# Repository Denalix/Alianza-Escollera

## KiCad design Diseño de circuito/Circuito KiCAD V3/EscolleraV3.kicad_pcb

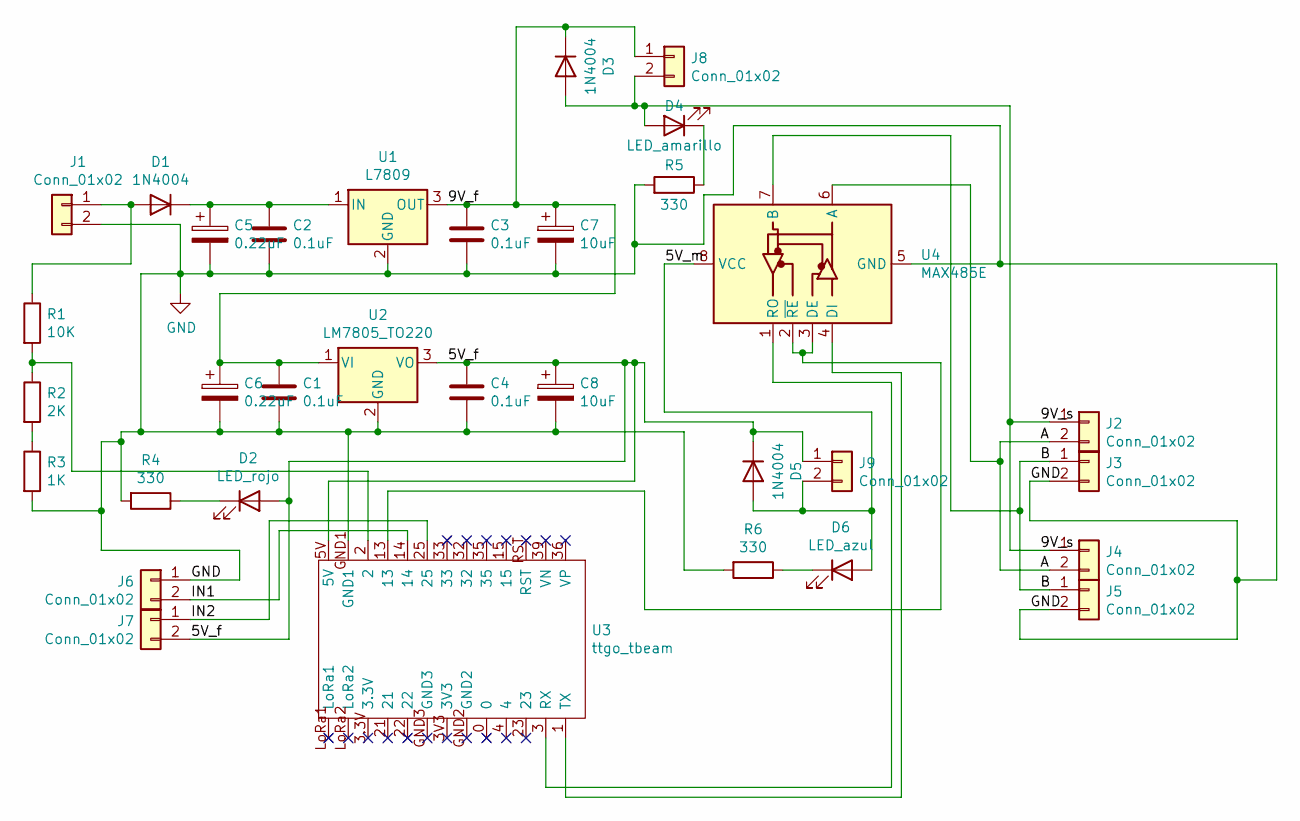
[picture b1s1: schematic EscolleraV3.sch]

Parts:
C1, C2, C3, C4: 0.1uF; C_Disc_D4.7mm_W2.5mm_P5.00mm
C5, C6: 0.22uF; C_Radial_D5.0mm_H11.0mm_P2.00mm
C7, C8: 10uF; C_Radial_D5.0mm_H11.0mm_P2.00mm
D1, D3, D5: 1N4004; D_DO-41_SOD81_P3.81mm_Vertical_AnodeUp
D2: LED_rojo; LED_D3.0mm
D4: LED_amarillo; LED_D3.0mm
D6: LED_azul; LED_D3.0mm
J1, J2, J3, J4, J5, J6, J7, J8, J9: Conn_01x02; bornera
R1: 10K; R_Axial_DIN0207_L6.3mm_D2.5mm_P7.62mm_Horizontal
R2: 2K; R_Axial_DIN0207_L6.3mm_D2.5mm_P7.62mm_Horizontal
R3: 1K; R_Axial_DIN0207_L6.3mm_D2.5mm_P7.62mm_Horizontal
R4, R5, R6: 330; R_Axial_DIN0207_L6.3mm_D2.5mm_P7.62mm_Horizontal
U1: L7809; TO-220-3_Vertical
U2: LM7805_TO220; TO-220-3_Vertical
U3: ttgo_tbeam
U4: MAX485E; max485_TTL_RS485

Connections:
/5V_f: C4.1, C8.1, D2.2 (A), D5.1 (K), J7.2, J9.1, U2.3 (VO), U3.5V
/5V_m: D5.2 (A), D6.2 (A), J9.2, U4.8 (VCC)
/9V_f: C1.1, C3.1, C6.1, C7.1, D3.1 (K), J8.1, U1.3 (OUT), U2.1 (VI)
/9V_s: D3.2 (A), D4.2 (A), J2.1, J4.1, J8.2
/A: J2.2, J4.2, U4.6 (A)
/B: J3.1, J5.1, U4.7 (B)
/IN1: J6.2, U3.14
/IN2: J7.1, U3.25
GND: C1.2, C2.2, C3.2, C4.2, C5.2, C6.2, C7.2, C8.2, J1.2, J3.2, J5.2, J6.1, R3.2, R4.2, R5.2, R6.2, U1.2 (GND), U2.2 (GND), U3.GND1, U4.5 (GND)
unnamed: C2.1, C5.1, D1.1 (K), U1.1 (IN)
unnamed: D1.2 (A), J1.1, R1.1
unnamed: D2.1 (K), R4.1
unnamed: D4.1 (K), R5.1
unnamed: D6.1 (K), R6.1
unnamed: R1.2, R2.1, U3.2
unnamed: R2.2, R3.1
unnamed: U3.1 (TX), U4.4 (DI)
unnamed: U3.3 (RX), U4.1 (RO)
unnamed: U3.13, U4.2 (~RE), U4.3 (DE)

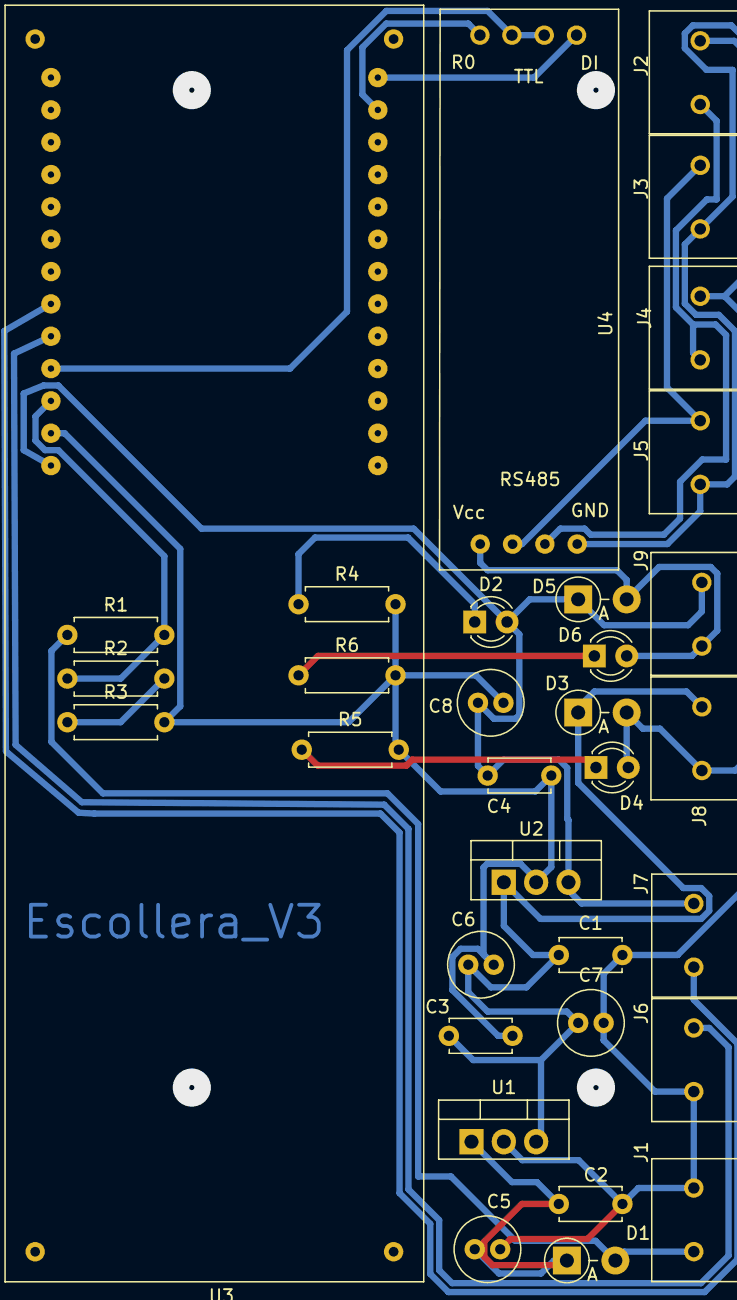
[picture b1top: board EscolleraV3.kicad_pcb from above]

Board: 2 copper layers, 33 parts (0 on the bottom side), 19 nets.

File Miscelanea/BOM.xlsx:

componente | imagen | Cantidad por boya | Precio estimado por unidad (pesos colombianos) | Total cantidad de elementos | Total precio por 3 boyas | Cantida de boyas | 3 | U2 | LM7805_TO220
MAX485 |  | 1 | 4500 | 3 | 13500 |  |  | J1 | Conn_01x02
LM7805 |  | 1 | 900 | 3 | 2700 |  |  | C2 | 0.1uF
LM7809 |  | 1 | 1000 | 3 | 3000 |  |  | C3 | 0.1uF
Condensador electrolítico 0.22 uF |  | 2 | 100 | 6 | 600 |  |  | C1 | 0.1uF
Condensador electrolítico 10 uF |  | 2 | 100 | 6 | 600 |  |  | C1 | 0.1uF
Condensador cerámico 104 (100nf o 0.1uf ) |  | 4 | 100 | 12 | 1200 |  |  | C4 | 0.1uF
Bornera de dos pines |  | 9 | 1000 | 27 | 27000 |  |  | U4 | MAX485E
Diodo 1N4004 |  | 3 | 100 | 9 | 900 |  |  | U3 | ttgo_tbeam
LED de chorro amarillo |  | 3 | 100 | 9 | 900 |  |  | U3 | ttgo_tbeam
LED de chorro rojo |  | 3 | 100 | 9 | 900 |  |  | U3 | ttgo_tbeam
LED de chorro azul |  | 3 | 100 | 9 | 900 |  |  | U3 | ttgo_tbeam
Resistencia 330 ohmios 1/4 de watt |  | 3 | 100 | 9 | 900 |  |  | U3 | ttgo_tbeam
Resistencia 1 kilo ohmio 1/4 de watt |  | 1 | 100 | 3 | 300 |  |  | U3 | ttgo_tbeam
Resistencia 10 kilo ohmios 1/4 de watt |  | 1 | 100 | 3 | 300 |  |  | U3 | ttgo_tbeam
Resistencia 2 kilo ohmios 1/4 de watt |  | 1 | 100 | 3 | 300 |  |  | U3 | ttgo_tbeam
módulo relé de dos canáles |  | 1 | 12500 | 3 | 37500 |  |  | U3 | ttgo_tbeam
jumpers amarillos |  | 3 | 300 | 9 | 2700 |  |  | U3 | ttgo_tbeam
jumpers azules |  | 3 | 300 | 9 | 2700 |  |  | U3 | ttgo_tbeam
jumpers verdes |  | 3 | 300 | 9 | 2700 |  |  | U3 | ttgo_tbeam
jumpers naranja |  | 3 | 300 | 9 | 2700 |  |  | U3 | ttgo_tbeam
Regleta de Pines Header Macho - Hembra 1x40 2.54mm |  | 1 | 1000 | 3 | 3000 |  |  | U3 | ttgo_tbeam
Termoencogible 5 mm diámetro por metro |  | 1 | 1200 | 3 | 3600 |  |  | U3 | ttgo_tbeam
Termoencogible 5 mm diámetro por metro |  | 1 | 3000 | 3 | 9000 |  |  | U3 | ttgo_tbeam
Malla desoldadora |  | 1 | 6500 | 3 | 19500 |  |  | U3 | ttgo_tbeam
Carreta de Soldadura de Estaño Solder 30 gr |  | 1 | 11000 | 3 | 33000 |  |  | U3 | ttgo_tbeam
Cautín 40W HQ |  | 1 | 35000 | 3 | 105000 |  |  | U3 | ttgo_tbeam
Tercera Mano con Soporte para Cautín, Pinzas y Lupa |  | 1 | 35000 | 3 | 105000 |  |  | U3 | ttgo_tbeam
Pomada para Soldar "La Única" 8 gr |  | 1 | 3000 | 3 | 9000 |  |  | U3 | ttgo_tbeam
Extractor Removedor de Soldadura Estaño - Plomo ZD190 |  | 1 | 8000 | 3 | 24000 |  |  | U3 | ttgo_tbeam
Batería seca 12V 5Ah |  | 1 |  | 3 | 0 |  |  | U3 | ttgo_tbeam
Multimetro Digital Uni-t Referencia Ut33c+ |  | 1 | 63000 | 3 | 189000 |  |  | U3 | ttgo_tbeam
Pinza de Punta Larga 4 Pulgadas - Marca Ranger |  | 1 | 15000 | 3 | 45000 |  |  | U3 | ttgo_tbeam
Pinza de Punta Curva 4 Pulgadas - Marca Ranger |  | 1 | 12500 | 3 | 37500 |  |  | U3 | ttgo_tbeam
Cortafrio 4 Pulgadas - Marca Ranger |  | 1 | 12500 | 3 | 37500 |  |  | U3 | ttgo_tbeam
Pelacable Ajustable 5" Calibres 10 AWG ~ 30 AWG |  | 1 | 12500 | 3 | 37500 |  |  | U3 | ttgo_tbeam
Total |  |  |  | 198 | 759900 |  |  | C5 | 0.22uF
 |  |  |  |  |  |  |  | C7 | 10uF
 |  |  |  |  |  |  |  | C6 | 0.22uF
 |  |  |  |  |  |  |  | C8 | 10uF
 |  |  |  |  |  |  |  | J2 | Conn_01x02
 |  |  |  |  |  |  |  | J3 | Conn_01x02
 |  |  |  |  |  |  |  | J4 | Conn_01x02
 |  |  |  |  |  |  |  | J5 | Conn_01x02
 |  |  |  |  |  |  |  | U1 | L7809
 |  |  |  |  |  |  |  | D5 | 1N4004
 |  |  |  |  |  |  |  | D3 | 1N4004
 |  |  |  |  |  |  |  | D1 | 1N4004
 |  |  |  |  |  |  |  | J8 | Conn_01x02
 |  |  |  |  |  |  |  | J9 | Conn_01x02
 |  |  |  |  |  |  |  | J6 | Conn_01x02
 |  |  |  |  |  |  |  | J7 | Conn_01x02
 |  |  |  |  |  |  |  | D4 | LED
 |  |  |  |  |  |  |  | D2 | LED
 |  |  |  |  |  |  |  | D6 | LED
 |  |  |  |  |  |  |  | R6 | 330
 |  |  |  |  |  |  |  | R4 | 330
 |  |  |  |  |  |  |  | R1 | 10K
 |  |  |  |  |  |  |  | R2 | 2K
 |  |  |  |  |  |  |  | R3 | 1K
 |  |  |  |  |  |  |  | R5 | 330

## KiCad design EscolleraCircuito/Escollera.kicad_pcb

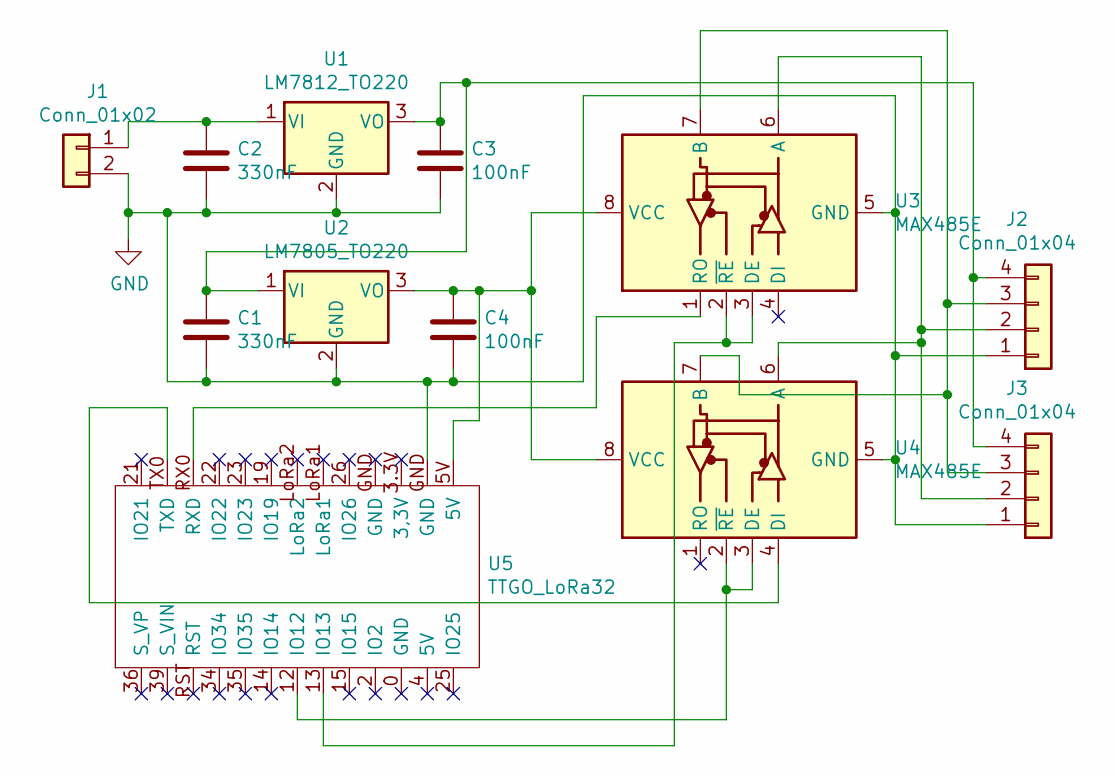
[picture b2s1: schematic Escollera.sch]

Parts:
C1, C2: 330nF; C_Disc_D4.7mm_W2.5mm_P5.00mm
C3, C4: 100nF; C_Disc_D4.7mm_W2.5mm_P5.00mm
J1: Conn_01x02; Molex_KK-396_A-41791-0002_1x02_P3.96mm_Vertical
J2, J3: Conn_01x04; Molex_KK-396_A-41791-0004_1x04_P3.96mm_Vertical
U1: LM7812_TO220; TO-220-3_Vertical
U2: LM7805_TO220; TO-220-3_Vertical
U3, U4: MAX485E; max485_TTL_RS485
U5: TTGO_LoRa32; TTGO

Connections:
GND: C1.2, C2.2, C3.2, C4.2, J1.2, J2.1, J3.1, U1.2 (GND), U2.2 (GND), U3.5 (GND), U4.5 (GND), U5.GND
unnamed: C1.1, C3.1, J2.4, J3.4, U1.3 (VO), U2.1 (VI)
unnamed: C2.1, J1.1, U1.1 (VI)
unnamed: C4.1, U2.3 (VO), U3.8 (VCC), U4.8 (VCC), U5.5V
unnamed: J2.2, J3.2, U3.6 (A), U4.6 (A)
unnamed: J2.3, J3.3, U3.7 (B), U4.7 (B)
unnamed: U3.1 (RO), U5.RX0 (RXD)
unnamed: U3.2 (~RE), U3.3 (DE), U5.13 (IO13)
unnamed: U4.2 (~RE), U4.3 (DE), U5.12 (IO12)
unnamed: U4.4 (DI), U5.TX0 (TXD)

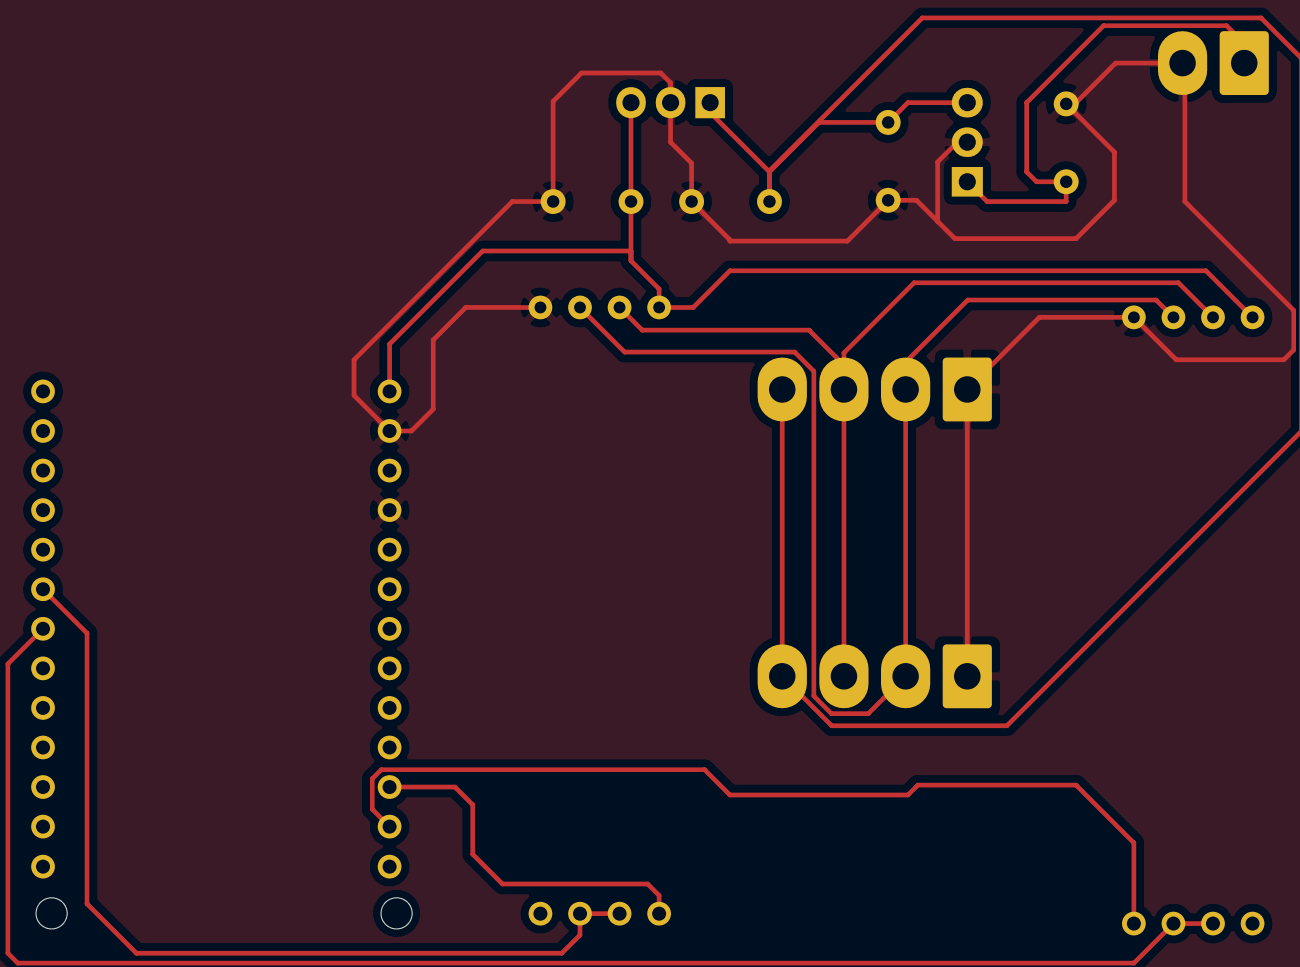
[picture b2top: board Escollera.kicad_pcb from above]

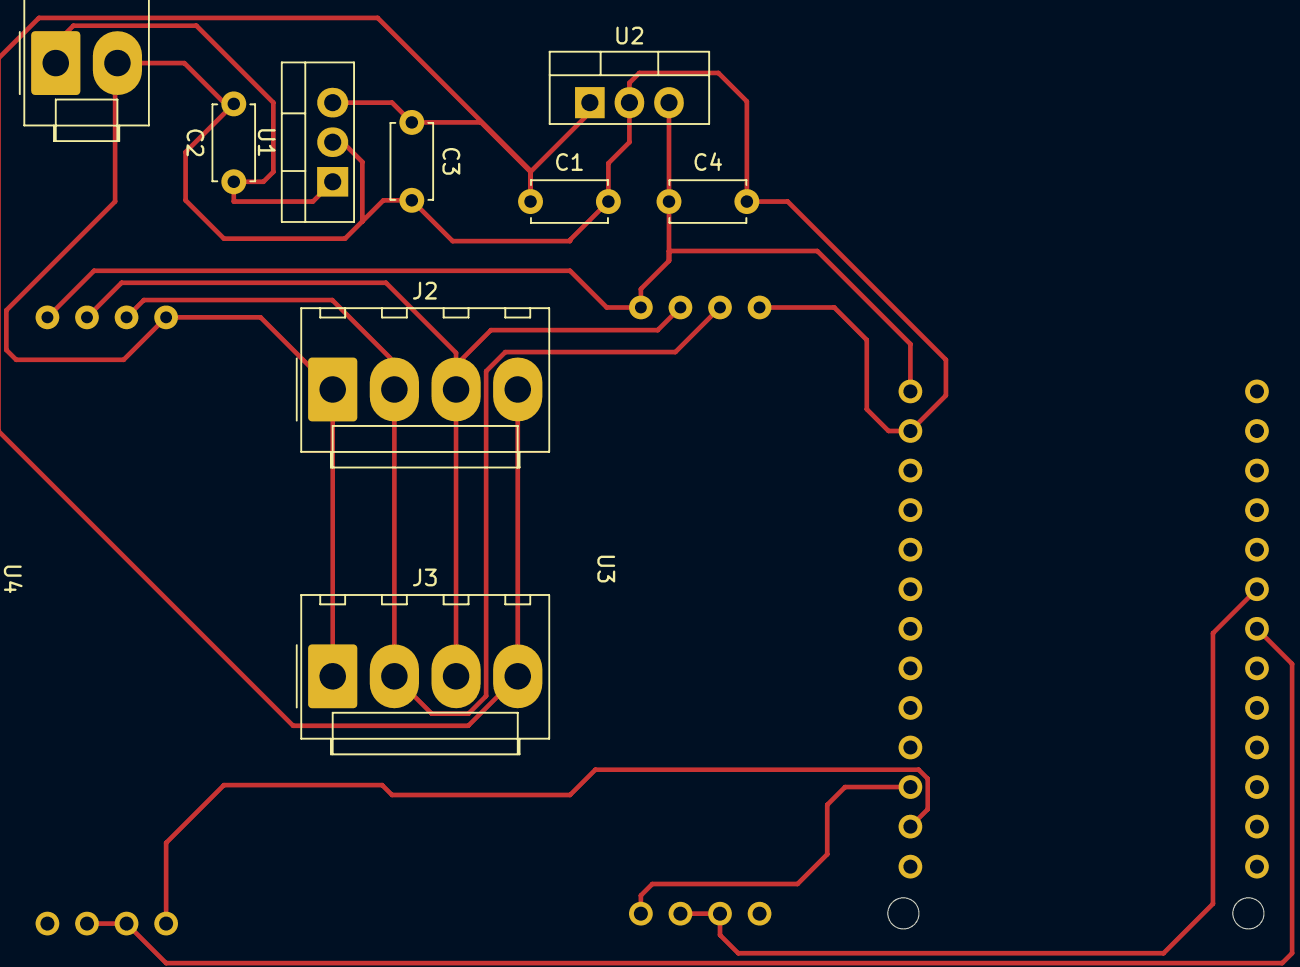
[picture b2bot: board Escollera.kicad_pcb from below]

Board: 2 copper layers, 12 parts (12 on the bottom side), 10 nets.

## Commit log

2021-11-28 primer commit
2021-12-16 pdfs del esquemático y la PCB
2021-12-18 actualización 17-12-2021
2021-12-18 datos de luz para paneles solares
2022-02-24 actualizacion de CAD y nueva carpeta de analisis energetico
2022-05-23 actualizacion analisis electrico
2022-06-30 codigo conexion TTGO - sondas
2022-12-08 reboot for V3
2022-12-08 reboot
2022-12-08 Análisis energético V3
2022-12-08 Circuito V3
2022-12-08 Miscelanea última
2022-12-08 Codigo V3
2022-12-08 calibracion y datasheets V3
2022-12-08 CAD V2
2022-12-08 Tesis y cambios V3
